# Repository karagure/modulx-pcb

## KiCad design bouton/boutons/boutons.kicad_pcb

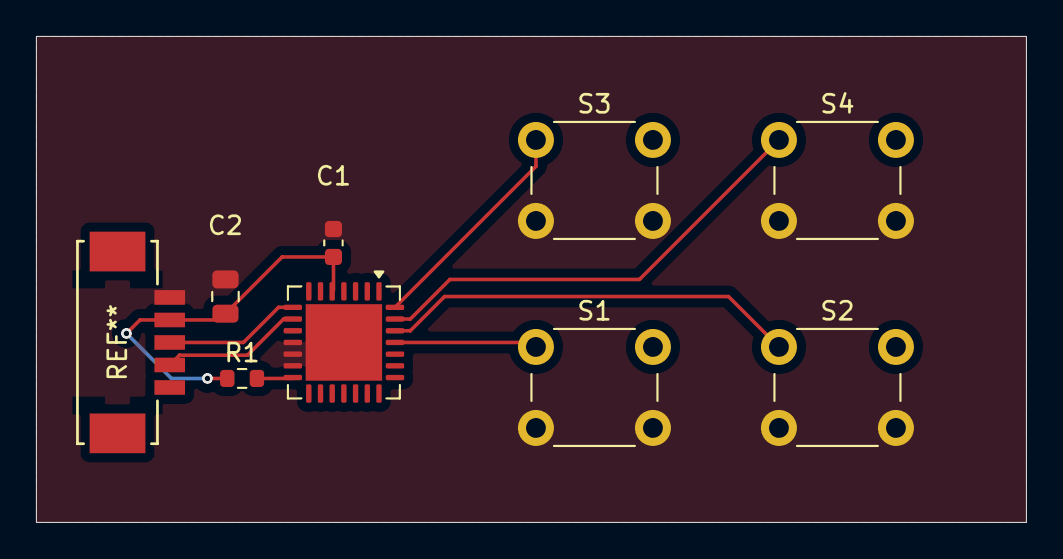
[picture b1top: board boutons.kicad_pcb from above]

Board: 2 copper layers, 55.0 x 27.0 mm, 8 parts (0 on the bottom side), 7 nets.

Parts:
C1: 100nF; C_0603_1608Metric
C2: 10uF; C_0805_2012Metric
R1: 10kΩ; R_0603_1608Metric
S1, S2, S3, S4: TL1105RF160Q94VO; SW_PUSH_6mm_H5mm
U1: MCP23017_ML; QFN-28-1EP_6x6mm_P0.65mm_EP4.25x4.25mm

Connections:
3.3V: C1.2, C2.2, R1.1, U1.5 (VDD)
GND: C1.1, C2.1, S1.2 (NO), S2.2 (NO), S3.2 (NO), S4.2 (NO), U1.6 (VSS), U1.11 (A0), U1.12 (A1), U1.13 (A2), U1.29 (EP)
unnamed: S1.1 (COM), U1.25 (GPB0)
unnamed: S2.1 (COM), U1.26 (GPB1)
unnamed: S3.1 (COM), U1.28 (GPB3)
unnamed: S4.1 (COM), U1.27 (GPB2)
unnamed: R1.2, U1.14 (~RESET)

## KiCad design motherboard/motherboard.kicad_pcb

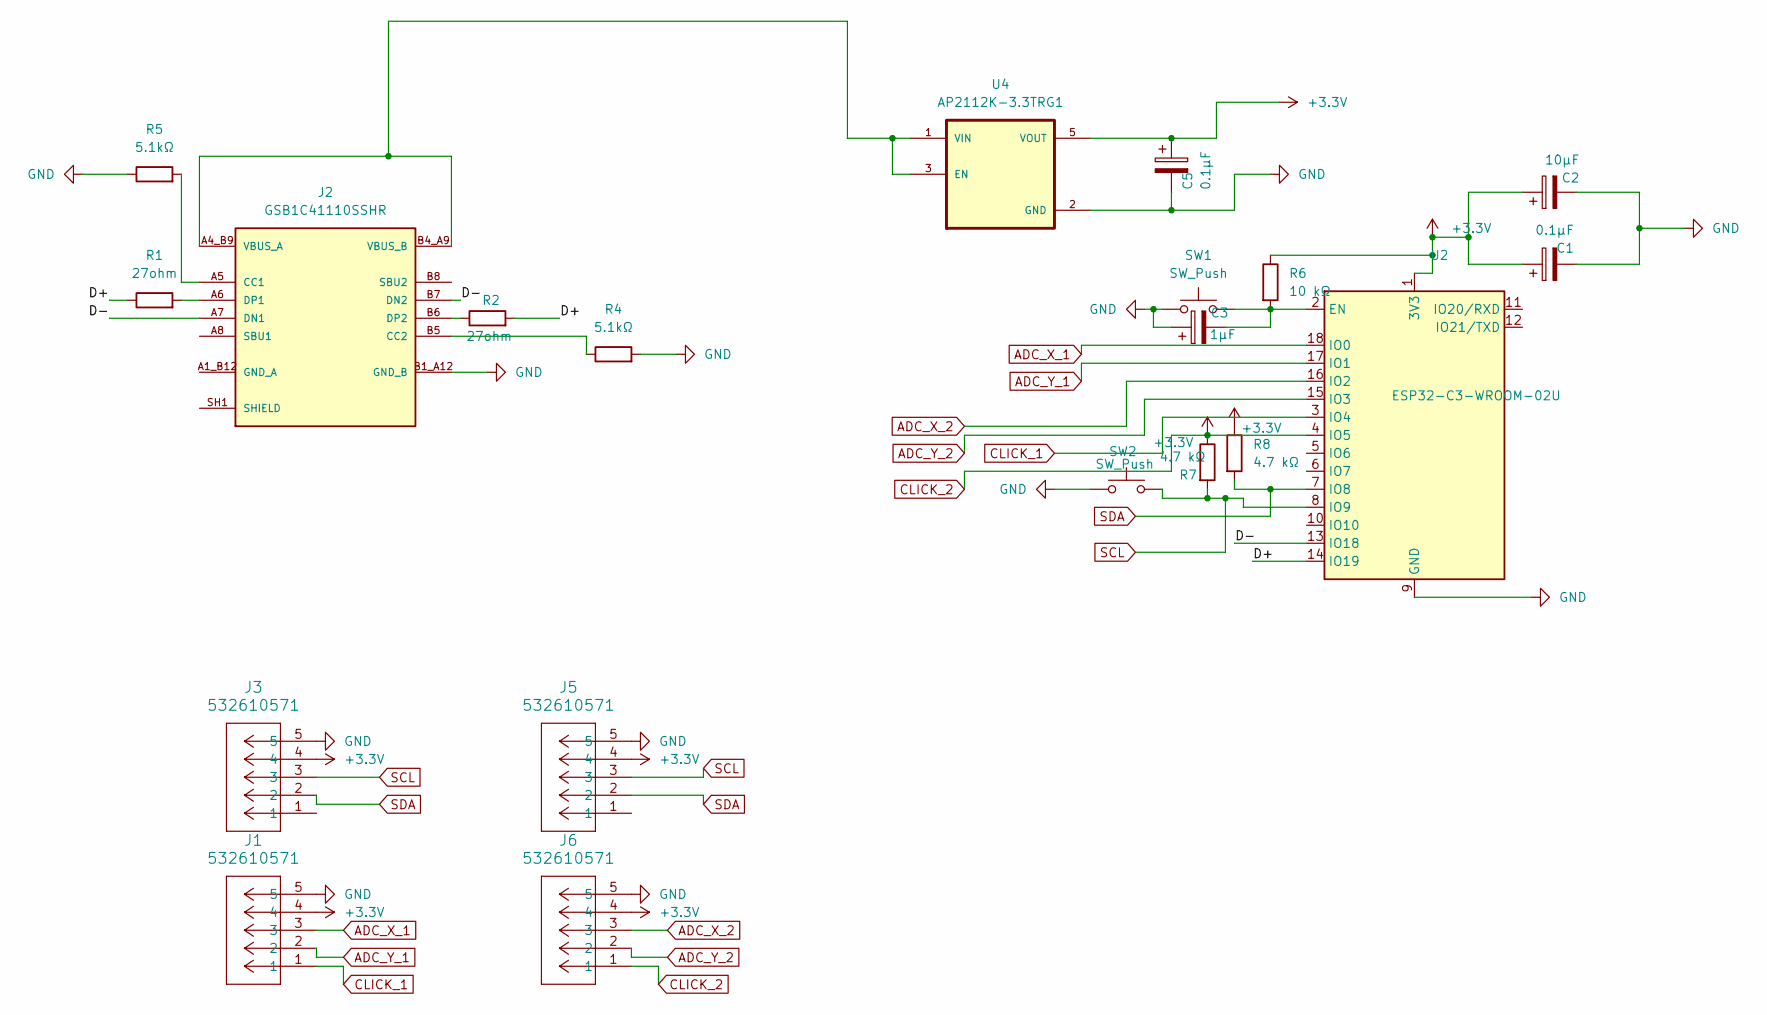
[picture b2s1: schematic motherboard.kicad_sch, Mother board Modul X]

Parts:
C1, C5: 0.1µF; C_0201_0603Metric
C2: 10µF; C_0201_0603Metric
C3: 1µF; C_0201_0603Metric
J1, J3, J5, J6: 532610571; CONN_532610001-SD_05_MOL
J2: GSB1C41110SSHR; AMPHENOL_GSB1C41110SSHR; PARTREV AX1; DigiKey_Part_Number 664-GSB1C41110SSHRCT-ND
R1, R2: 27ohm; R_0201_0603Metric
R4, R5: 5.1kΩ; R_0201_0603Metric
R6: 10 kΩ; R_0201_0603Metric
R7, R8: 4.7 kΩ; R_0201_0603Metric
SW1, SW2: SW_Push; SW_SPST_PTS810
U2: ESP32-C3-WROOM-02U
U4: AP2112K-3.3TRG1; SOT95P285X140-5N; PARTREV 2-2

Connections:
/D+: R1.1, R2.2, U2.14 (IO19)
/D-: J2.A7 (DN1), J2.B7 (DN2), U2.13 (IO18)
ADC_X_1: J1.3, U2.18 (IO0)
ADC_X_2: J6.3, U2.16 (IO2)
ADC_Y_1: J1.2, U2.17 (IO1)
ADC_Y_2: J6.2, U2.15 (IO3)
CLICK_1: J1.1, U2.3 (IO4)
CLICK_2: C1.1, C2.1, C5.1, J1.4, J3.4, J5.4, J6.1, J6.4, R6.1, R7.1, R8.1, U2.1 (3V3), U2.4 (IO5), U4.5 (VOUT)
GND: C1.2, C2.2, C3.1, C5.2, J1.5, J2.B1_A12 (GND_B), J3.5, J5.5, J6.5, R4.2, R5.1, SW1.1, SW2.1, U2.9 (GND), U2.19 (GND), U4.2 (GND)
unnamed: J2.A5 (CC1), R5.2
unnamed: J2.B5 (CC2), R4.1
unnamed: J2.A6 (DP1), R1.2
unnamed: J2.B6 (DP2), R2.1
unnamed: J2.SH1 (SHIELD), J2.SH2 (SHIELD), J2.SH3 (SHIELD), J2.SH4 (SHIELD)
unnamed: J2.A4_B9 (VBUS_A), J2.B4_A9 (VBUS_B), U4.1 (VIN), U4.3 (EN)
unnamed: C3.2, R6.2, SW1.2, U2.2 (EN)
SCL: J3.3, J5.3, R7.2, SW2.2, U2.8 (IO9)
SDA: J3.2, J5.2, R8.2, U2.7 (IO8)

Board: 2 copper layers, 20 parts (0 on the bottom side), 18 nets, no tracks yet.

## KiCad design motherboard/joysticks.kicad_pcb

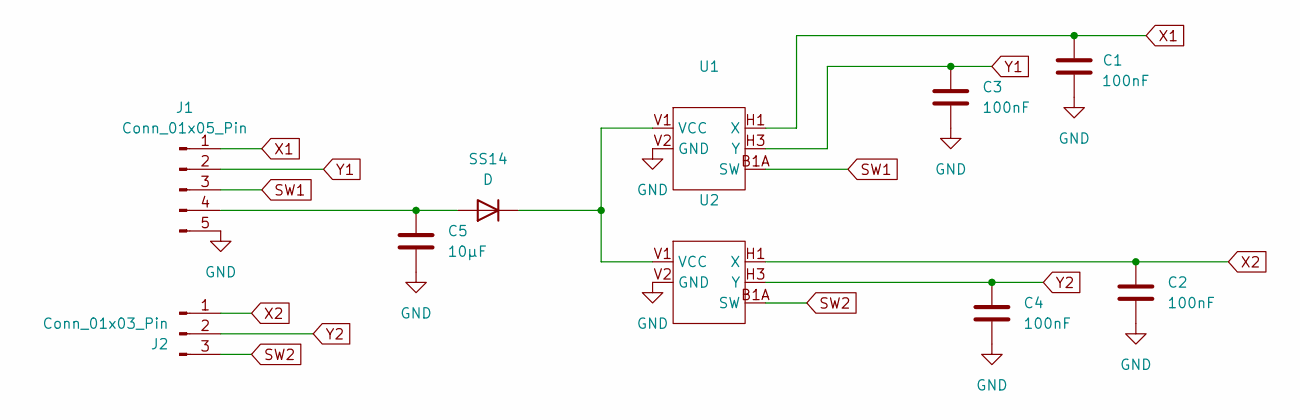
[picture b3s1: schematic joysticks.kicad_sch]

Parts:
C1, C2, C3, C4: 100nF; C_0805_2012Metric_Pad1.18x1.45mm_HandSolder
C5: 10µF; C_0805_2012Metric_Pad1.18x1.45mm_HandSolder
J1: Conn_01x05_Pin; Molex_PicoBlade_53047-0510_1x05_P1.25mm_Vertical
J2: Conn_01x03_Pin; Molex_PicoBlade_53047-0310_1x03_P1.25mm_Vertical
SS14: D; D_SMA
U1, U2: XDCR_COM-09032

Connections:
GND: C1.2, C2.2, C3.2, C4.2, C5.2, J1.5, U1.V2 (GND), U2.V2 (GND)
unnamed: C5.1, J1.4, SS14.2 (A)
unnamed: SS14.1 (K), U1.V1 (VCC), U2.V1 (VCC)
SW1: J1.3, U1.B1A (SW)
SW2: J2.3, U2.B1A (SW)
X1: C1.1, J1.1, U1.H1 (X)
X2: C2.1, J2.1, U2.H1 (X)
Y1: C3.1, J1.2, U1.H3 (Y)
Y2: C4.1, J2.2, U2.H3 (Y)

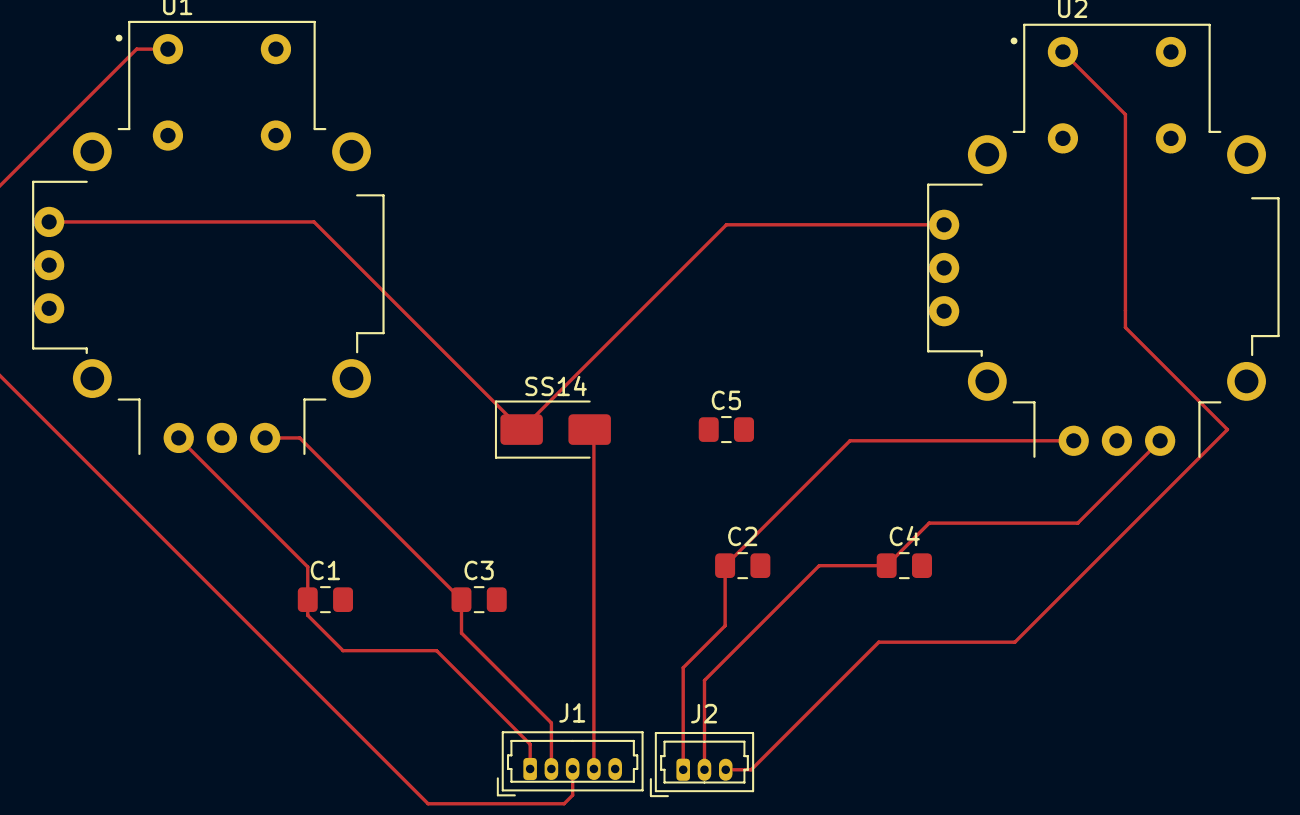
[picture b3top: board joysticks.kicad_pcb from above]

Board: 2 copper layers, 10 parts (0 on the bottom side), 9 nets.

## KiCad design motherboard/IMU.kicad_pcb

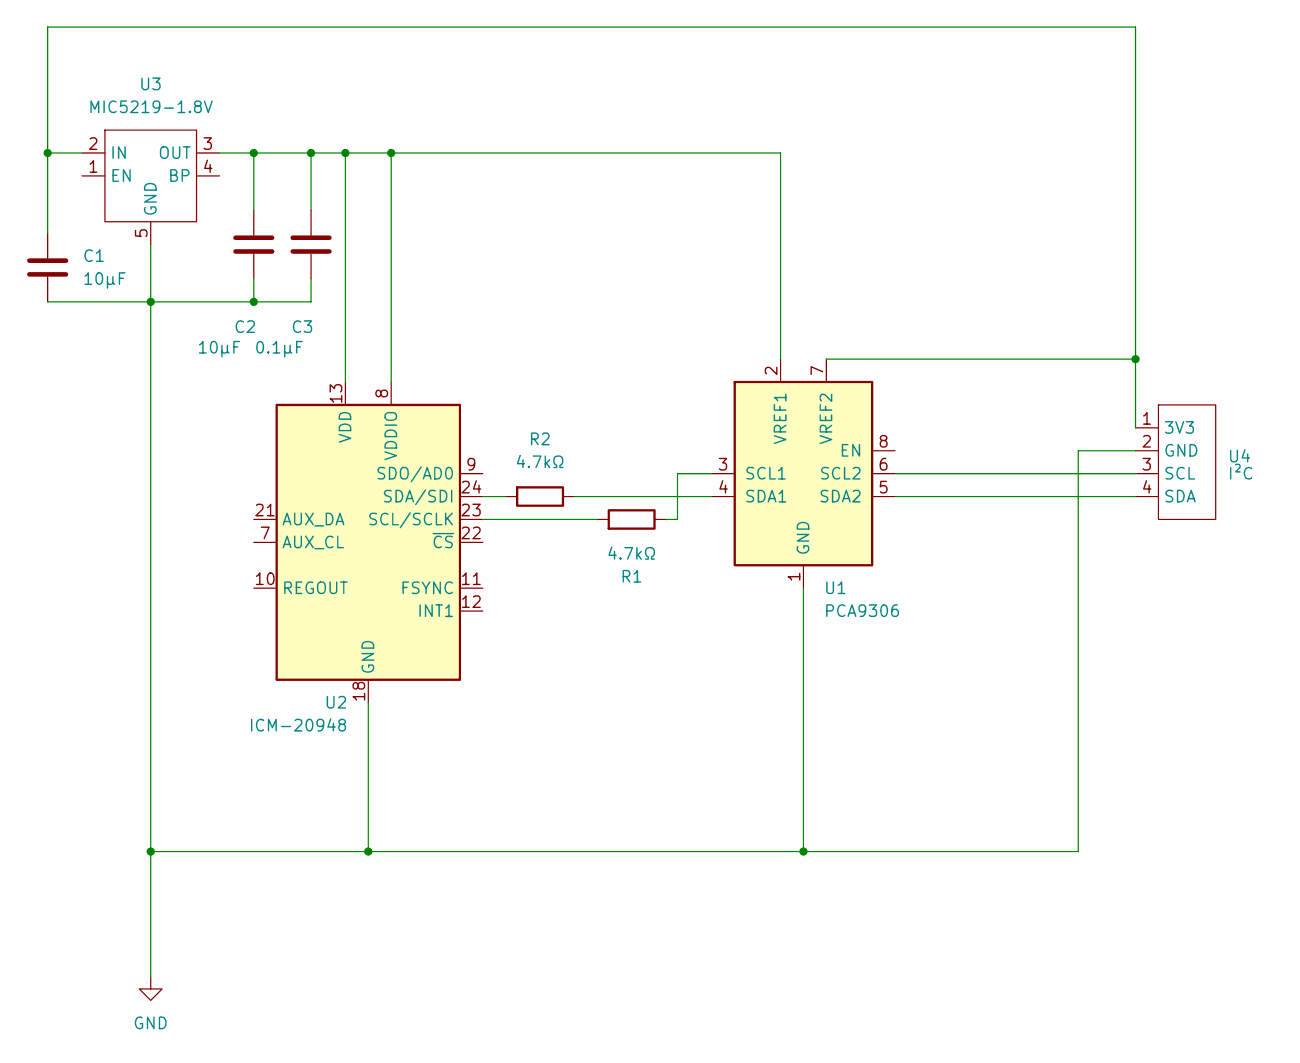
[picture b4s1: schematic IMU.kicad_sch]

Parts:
C1, C2: 10µF; C_0805_2012Metric
C3: 0.1µF; C_0805_2012Metric
R1, R2: 4.7kΩ; R_0805_2012Metric
U1: PCA9306; SOT-23-8
U2: ICM-20948; InvenSense_QFN-24_3x3mm_P0.4mm
U3: MIC5219-1.8V; SOT-23-5
U4: I²C; Molex_PicoBlade_53261-0471_1x04-1MP_P1.25mm_Horizontal

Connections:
GND: C1.1, C2.2, C3.2, U1.1 (GND), U2.18 (GND), U2.20 (GND), U3.5 (GND), U4.2 (GND)
unnamed: R1.1, U1.3 (SCL1)
unnamed: U1.6 (SCL2), U4.3 (SCL)
unnamed: R2.1, U1.4 (SDA1)
unnamed: U1.5 (SDA2), U4.4 (SDA)
unnamed: C2.1, C3.1, U1.2 (VREF1), U2.8 (VDDIO), U2.13 (VDD), U3.3 (OUT)
unnamed: C1.2, U1.7 (VREF2), U3.2 (IN), U4.1 (3V3)
unnamed: R1.2, U2.23 (SCL/SCLK)
unnamed: R2.2, U2.24 (SDA/SDI)

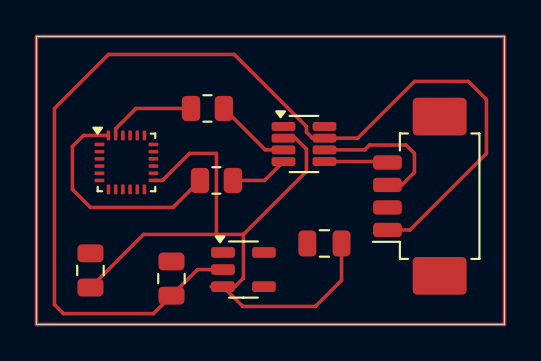
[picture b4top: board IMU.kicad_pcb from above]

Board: 2 copper layers, 26.0 x 16.0 mm, 9 parts (0 on the bottom side), 9 nets.

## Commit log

2026-01-14 Première sauvegarde complète du projet
2026-01-14 fix : change composant
    for next day :
    - fix molex connector
    - fix esp32 routing
    - set pcb design
2026-01-18 update schema
2026-01-19 fix : add connector i2c + button boot & reset
2026-01-19 fix : delete fusible (danger for esp32)
2026-01-24 fix : 3d model and footprint
2026-02-13 add button pcb
2026-02-24 create gerber files
